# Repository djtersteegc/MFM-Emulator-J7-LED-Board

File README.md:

Simple PCB for the Drive 1 and Drive 2 select LED's exposed on the J7 expansion connector of [David Gesswein's MFM emulator](https://www.pdp8online.com/mfm/).  Plugs directly into the connector and uses 0805 SMD components for easier hand soldering.

I used 330R resistors which were plenty bright with the green LED's. Just make sure to limit current to no more than 6ma since these are driven right from the BeagleBone GPIO's. You can also use the board as a breakout to pin headers and install external LED's instead of the SMD mounted ones.

If you have a 3D printer, I also included a keyed sleeve that slides over a standard 2x10 2.54mm female pin socket and prevents you from potentially misaligning the board by one pin in the male IDC box socket.

### BOM

https://djtersteegc.github.io/MFM-Emulator-J7-LED-Board/ibom-v1.0.html

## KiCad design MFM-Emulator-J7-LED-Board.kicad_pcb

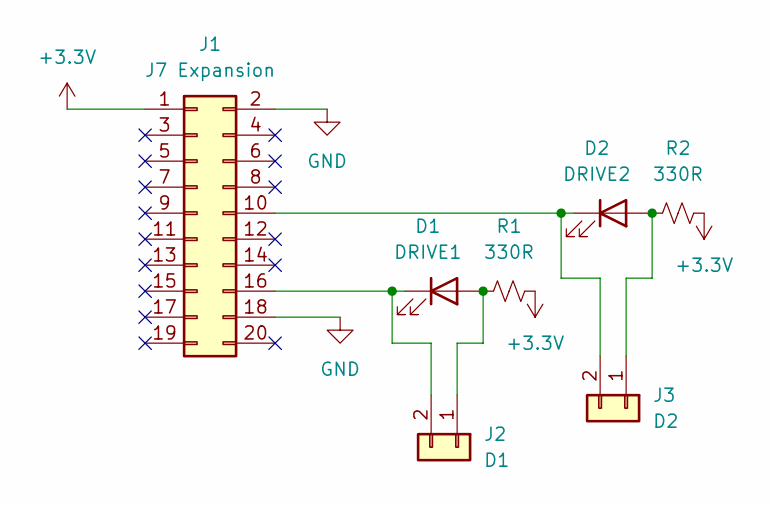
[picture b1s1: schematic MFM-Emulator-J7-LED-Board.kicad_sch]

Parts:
D1: DRIVE1; LED_0805_2012Metric_Pad1.15x1.40mm_HandSolder
D2: DRIVE2; LED_0805_2012Metric_Pad1.15x1.40mm_HandSolder
J1: J7 Expansion; PinSocket_2x10_P2.54mm_Vertical
J2: D1; PinHeader_1x02_P2.54mm_Vertical
J3: D2; PinHeader_1x02_P2.54mm_Vertical
R1, R2: 330R; R_0805_2012Metric_Pad1.20x1.40mm_HandSolder

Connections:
+3.3V: J1.1, R1.2, R2.2
GND: J1.2, J1.18
unnamed: D1.2 (A), J2.1, R1.1
unnamed: D1.1 (K), J1.16, J2.2
unnamed: D2.2 (A), J3.1, R2.1
unnamed: D2.1 (K), J1.10, J3.2

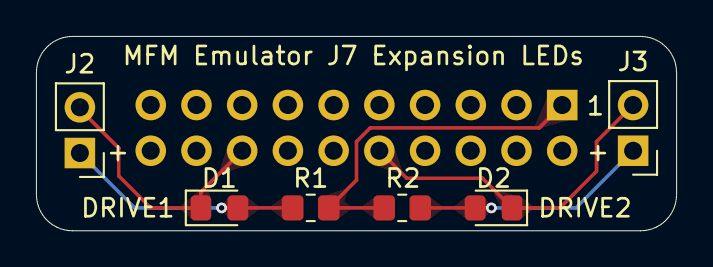
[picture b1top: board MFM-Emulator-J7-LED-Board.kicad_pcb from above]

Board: 2 copper layers, 35.6 x 10.8 mm, 7 parts (1 on the bottom side), 6 nets.

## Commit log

2025-02-02 v1.0, tested and working
2025-02-03 Add social image
